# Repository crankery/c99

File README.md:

# Mini Mini Cortex 

***Note: Do not build this thing, I am just experimenting.***

Just a silly project really. Trying to squeeze Stuart Conner's [Mini Cortex](https://www.stuartconner.me.uk/mini_cortex/mini_cortex.htm) down
to a smaller form factor. Really, for no good reason.

I am going to attempt to add a different storage mechanism as CF cards are a bit hard to work with these days. To this end, there's an expansion
connector on this thing which is intended to have a stack of expansions plugged in from below.

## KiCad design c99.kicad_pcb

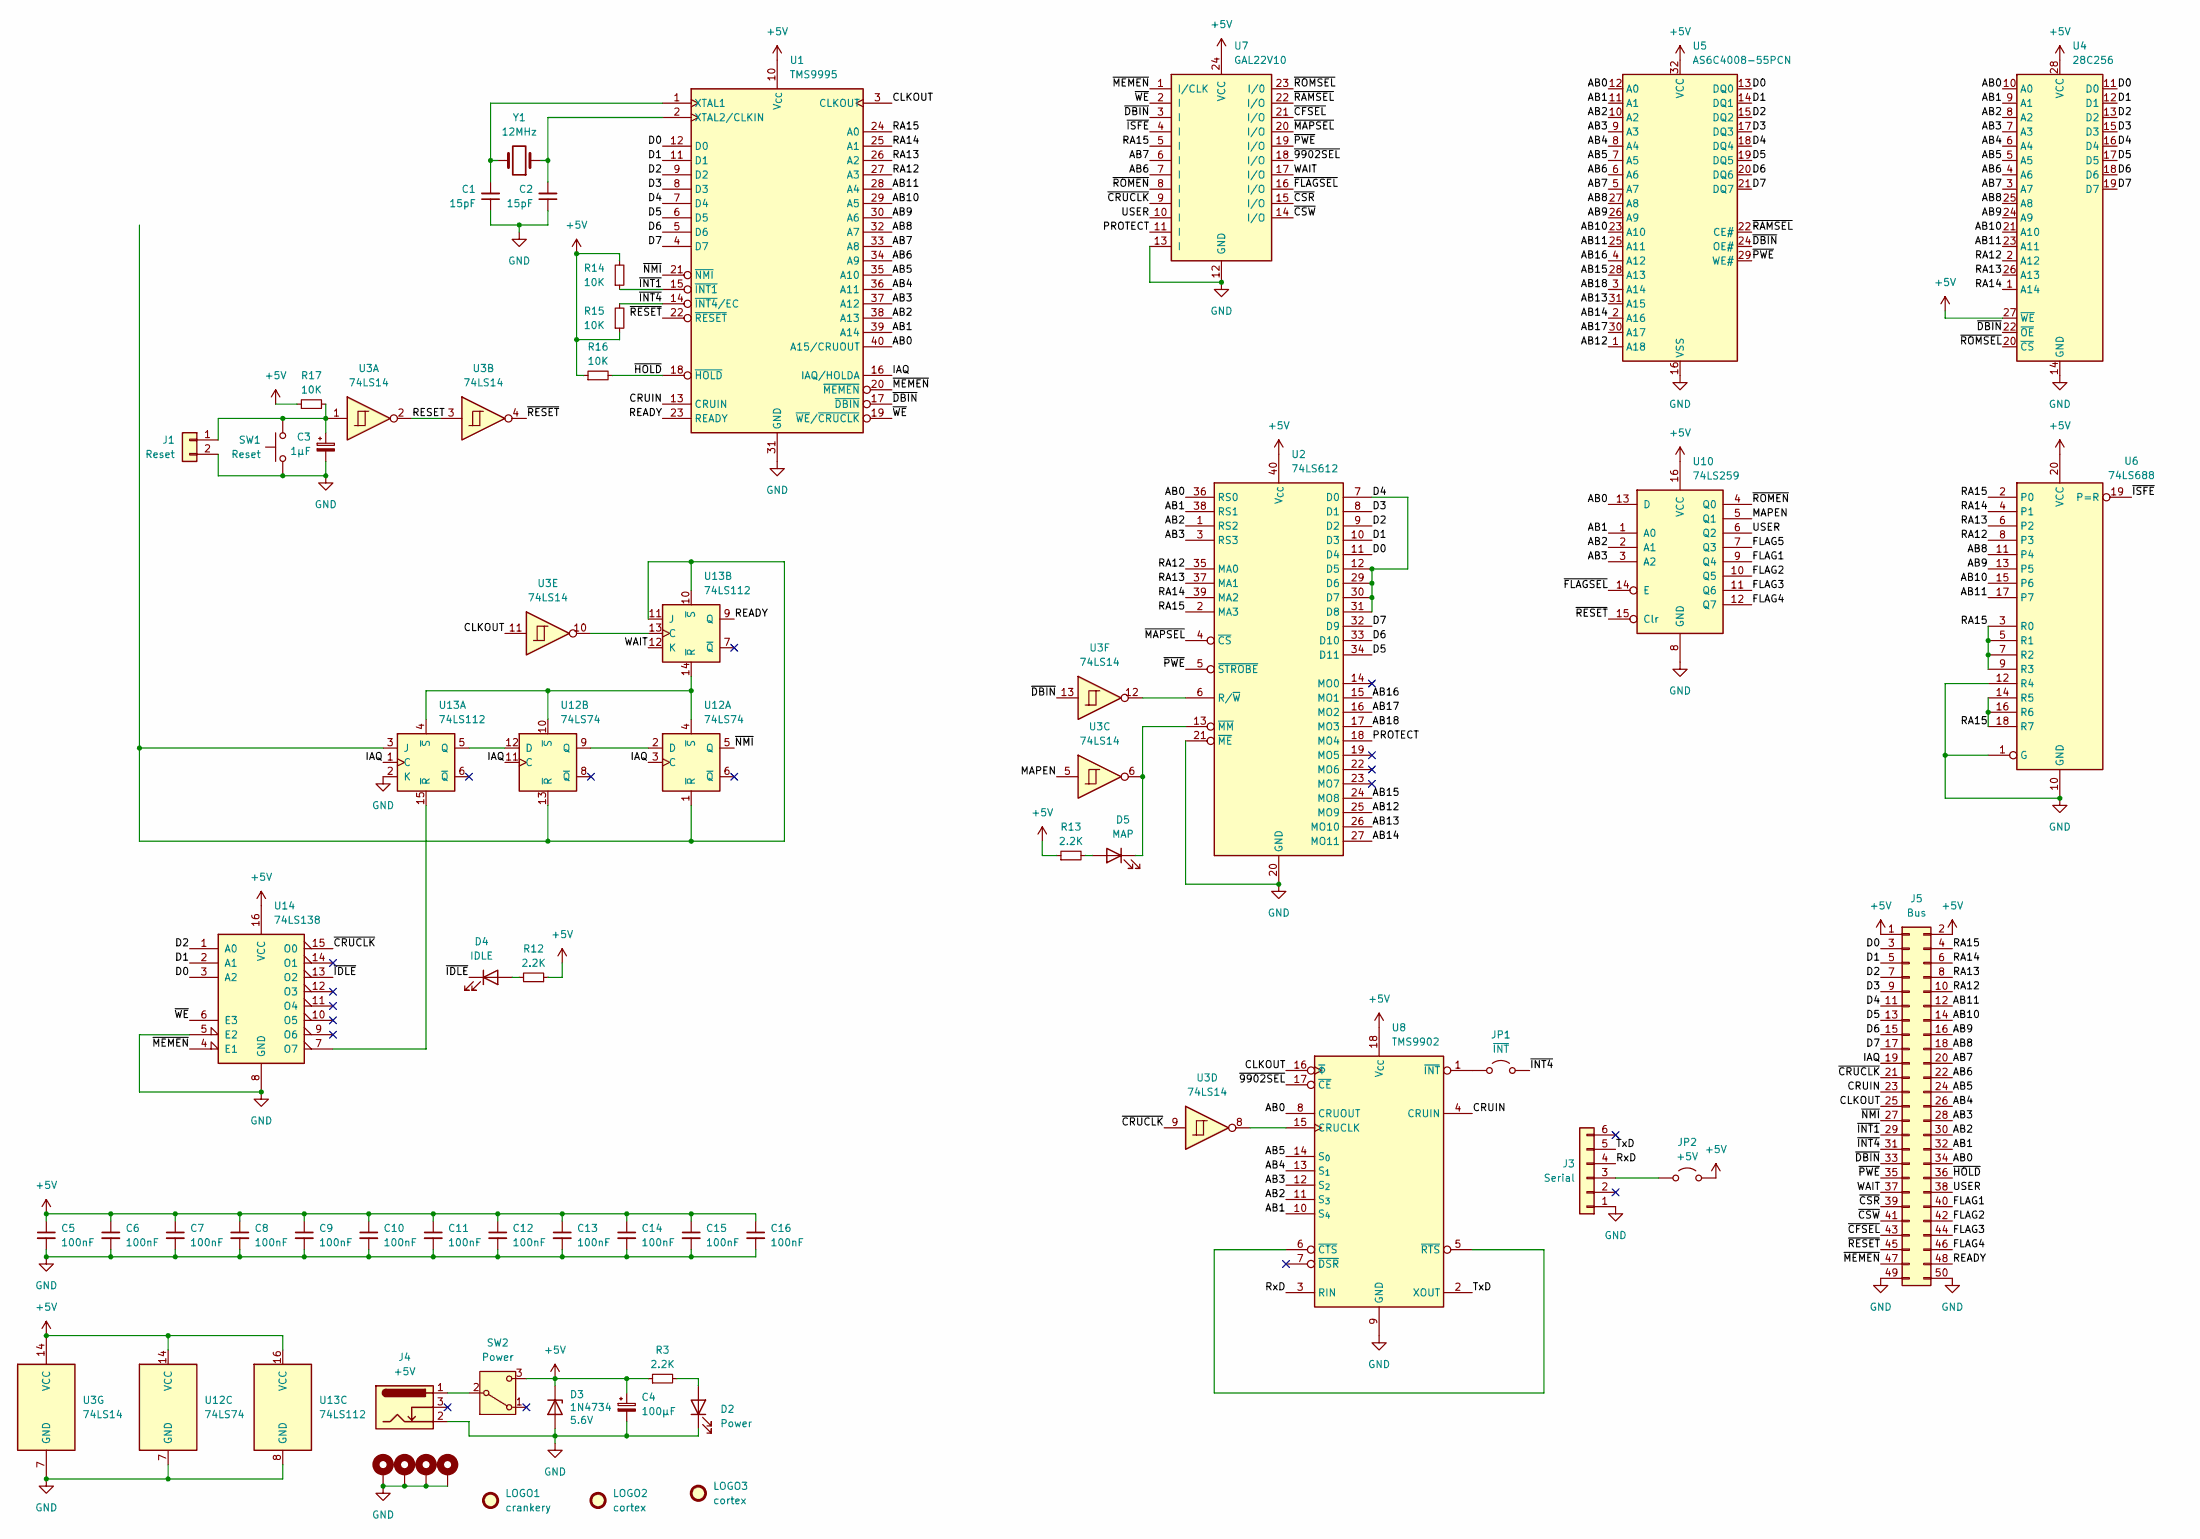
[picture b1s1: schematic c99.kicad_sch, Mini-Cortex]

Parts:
C1, C2: 15pF; C_Disc_D4.3mm_W1.9mm_P5.00mm
C3: 1µF; CP_Radial_D5.0mm_P2.00mm
C4: 100µF; CP_Radial_D5.0mm_P2.00mm
C5, C6, C7, C8, C9, C10, C11, C12, C13, C14, C15, C16: 100nF; C_Disc_D4.3mm_W1.9mm_P5.00mm
D2: Power; LED_D3.0mm
D3: 1N4734; D_DO-41_SOD81_P7.62mm_Horizontal
D4: IDLE; LED_D3.0mm
D5: MAP; LED_D3.0mm
H1, H2, H3, H4: MountingHole_Pad; MountingHole_2.7mm_M2.5_DIN965_Pad
J1: Reset; JST_PH_B2B-PH-K_1x02_P2.00mm_Vertical
J3: Serial; PinSocket_1x06_P2.54mm_Horizontal
J4: +5V; BarrelJack_Horizontal
J5: Bus; PinHeader_2x25_P2.54mm_Vertical
JP1: ~{INT}; PinHeader_1x02_P2.54mm_Vertical
JP2: +5V; PinHeader_1x02_P2.54mm_Vertical
LOGO1: crankery; crankery_small
LOGO2: cortex
LOGO3: cortex; eti
R3, R12, R13: 2.2K; R_Axial_DIN0204_L3.6mm_D1.6mm_P5.08mm_Horizontal
R14, R15, R16, R17: 10K; R_Axial_DIN0204_L3.6mm_D1.6mm_P5.08mm_Horizontal
SW1: Reset; SW_Tactile_SPST_Angled_PTS645Vx39-2LFS
SW2: Power; SW_2AS1T2A1M6QES
U1: TMS9995; DIP-40_W15.24mm
U2: 74LS612; DIP-40_W15.24mm
U3: 74LS14; DIP-14_W7.62mm
U4: 28C256; DIP-28_W15.24mm
U5: AS6C4008-55PCN; DIP-32_W15.24mm
U6: 74LS688; DIP-20_W7.62mm
U7: GAL22V10; DIP-24_W7.62mm
U8: TMS9902; DIP-18_W7.62mm
U10: 74LS259; DIP-16_W7.62mm
U12: 74LS74; DIP-14_W7.62mm
U13: 74LS112; DIP-16_W7.62mm
U14: 74LS138; DIP-16_W7.62mm
Y1: 12MHz; Crystal_HC49-U_Vertical

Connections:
+5V: C4.1, C5.1, C6.1, C7.1, C8.1, C9.1, C10.1, C11.1, C12.1, C13.1, C14.1, C15.1, C16.1, D3.1 (K), J5.1, J5.2, JP2.2 (B), R3.1, R12.1, R13.1, R14.2, R15.1, R16.1, R17.1, SW2.3 (C), U1.10 (V_{CC}), U2.40 (V_{CC}), U3.14 (VCC), U4.27 (~WE), U4.28 (VCC), U5.32 (VCC), U6.20 (VCC), U7.24 (VCC), U8.18 (V_{CC}), U10.16 (VCC), U12.14 (VCC), U13.16 (VCC), U14.16 (VCC)
/AB0: J5.34, U1.40 (A15/CRUOUT), U2.36 (RS0), U4.10 (A0), U5.12 (A0), U8.8 (CRUOUT), U10.13 (D)
/AB1: J5.32, U1.39 (A14), U2.38 (RS1), U4.9 (A1), U5.11 (A1), U8.10 (S_{4}), U10.1 (A0)
/AB2: J5.30, U1.38 (A13), U2.1 (RS2), U4.8 (A2), U5.10 (A2), U8.11 (S_{3}), U10.2 (A1)
/AB3: J5.28, U1.37 (A12), U2.3 (RS3), U4.7 (A3), U5.9 (A3), U8.12 (S_{2}), U10.3 (A2)
/AB4: J5.26, U1.36 (A11), U4.6 (A4), U5.8 (A4), U8.13 (S_{1})
/AB5: J5.24, U1.35 (A10), U4.5 (A5), U5.7 (A5), U8.14 (S_{0})
/AB6: J5.22, U1.34 (A9), U4.4 (A6), U5.6 (A6), U7.7 (I)
/AB7: J5.20, U1.33 (A8), U4.3 (A7), U5.5 (A7), U7.6 (I)
/AB8: J5.18, U1.32 (A7), U4.25 (A8), U5.27 (A8), U6.11 (P4)
/AB9: J5.16, U1.30 (A6), U4.24 (A9), U5.26 (A9), U6.13 (P5)
/AB10: J5.14, U1.29 (A5), U4.21 (A10), U5.23 (A10), U6.15 (P6)
/AB11: J5.12, U1.28 (A4), U4.23 (A11), U5.25 (A11), U6.17 (P7)
/AB12: U2.25 (MO9), U5.1 (A18)
/AB13: U2.26 (MO10), U5.31 (A15)
/AB14: U2.27 (MO11), U5.2 (A16)
/AB15: U2.24 (MO8), U5.28 (A13)
/AB16: U2.15 (MO1), U5.4 (A12)
/AB17: U2.16 (MO2), U5.30 (A17)
/AB18: U2.17 (MO3), U5.3 (A14)
/CLKOUT: J5.25, U1.3 (CLKOUT), U3.11, U8.16 (~Φ)
/CRUIN: J5.23, U1.13 (CRUIN), U8.4 (CRUIN)
/D0: J5.3, U1.12 (D0), U2.11 (D4), U4.11 (D0), U5.13 (DQ0), U14.3 (A2)
/D1: J5.5, U1.11 (D1), U2.10 (D3), U4.12 (D1), U5.14 (DQ1), U14.2 (A1)
/D2: J5.7, U1.9 (D2), U2.9 (D2), U4.13 (D2), U5.15 (DQ2), U14.1 (A0)
/D3: J5.9, U1.8 (D3), U2.8 (D1), U4.15 (D3), U5.17 (DQ3)
/D4: J5.11, U1.7 (D4), U2.7 (D0), U2.12 (D5), U2.29 (D6), U2.30 (D7), U2.31 (D8), U4.16 (D4), U5.18 (DQ4)
/D5: J5.13, U1.6 (D5), U2.34 (D11), U4.17 (D5), U5.19 (DQ5)
/D6: J5.15, U1.5 (D6), U2.33 (D10), U4.18 (D6), U5.20 (DQ6)
/D7: J5.17, U1.4 (D7), U2.32 (D9), U4.19 (D7), U5.21 (DQ7)
/FLAG1: J5.40, U10.9 (Q4)
/FLAG2: J5.42, U10.10 (Q5)
/FLAG3: J5.44, U10.11 (Q6)
/FLAG4: J5.46, U10.12 (Q7)
/FLAG5: U10.7 (Q3)
/IAQ: J5.19, U1.16 (IAQ/HOLDA), U12.3 (C), U12.11 (C), U13.1 (C)
/MAPEN: U3.5, U10.5 (Q1)
/PROTECT: U2.18 (MO4), U7.11 (I)
/RA12: J5.10, U1.27 (A3), U2.35 (MA0), U4.2 (A12), U6.8 (P3)
/RA13: J5.8, U1.26 (A2), U2.37 (MA1), U4.26 (A13), U6.6 (P2)
/RA14: J5.6, U1.25 (A1), U2.39 (MA2), U4.1 (A14), U6.4 (P1)
/RA15: J5.4, U1.24 (A0), U2.2 (MA3), U6.2 (P0), U6.3 (R0), U6.5 (R1), U6.7 (R2), U6.9 (R3), U6.14 (R5), U6.16 (R6), U6.18 (R7), U7.5 (I)
/READY: J5.48, U1.23 (READY), U13.9 (Q)
/RESET: U3.2, U3.3
/RxD: J3.4, U8.3 (RIN)
/TxD: J3.5, U8.2 (XOUT)
/USER: J5.38, U7.10 (I), U10.6 (Q2)
/WAIT: J5.37, U7.17 (I/O), U13.12 (K)
/~9902SEL: U7.18 (I/O), U8.17 (~CE)
/~CFSEL: J5.43, U7.21 (I/O)
/~CRUCLK: J5.21, U3.9, U7.9 (I), U14.15 (O0)
/~CSR: J5.39, U7.15 (I/O)
/~CSW: J5.41, U7.14 (I/O)
/~DBIN: J5.33, U1.17 (~DBIN), U3.13, U4.22 (~OE), U5.24 (OE#), U7.3 (I)
/~FLAGSEL: U7.16 (I/O), U10.14 (E)
/~HOLD: J5.36, R16.2, U1.18 (~HOLD)
/~IDLE: D4.1 (K), U14.13 (O2)
/~INT1: J5.29, R14.1, U1.15 (~INT1)
/~INT4: J5.31, JP1.2 (B), R15.2, U1.14 (~INT4/EC)
/~ISFE: U6.19 (P=R), U7.4 (I)
/~MAPSEL: U2.4 (~CS), U7.20 (I/O)
/~MEMEN: J5.47, U1.20 (~MEMEN), U7.1 (I/CLK), U14.4 (E1)
/~NMI: J5.27, U1.21 (~NMI), U12.5 (Q)
/~PWE: J5.35, U2.5 (~STROBE), U5.29 (WE#), U7.19 (I/O)
/~RAMSEL: U5.22 (CE#), U7.22 (I/O)
/~RESET: J5.45, U1.22 (~RESET), U3.4, U10.15 (Clr)
/~ROMEN: U7.8 (I), U10.4 (Q0)
/~ROMSEL: U4.20 (~CS), U7.23 (I/0)
/~WE: U1.19 (~WE/~CRUCLK), U7.2 (I), U14.6 (E3)
GND: C1.1, C2.1, C3.2, C4.2, C5.2, C6.2, C7.2, C8.2, C9.2, C10.2, C11.2, C12.2, C13.2, C14.2, C15.2, C16.2, D2.1 (K), D3.2 (A), H1.1 (1_1), H2.1 (1_1), H3.1 (1_1), H4.1 (1_1), J1.2, J3.1, J4.2, J5.49, J5.50, SW1.1, U1.31 (GND), U2.20 (GND), U2.21 (~ME), U3.7 (GND), U4.14 (GND), U5.16 (VSS), U6.1 (G), U6.10 (GND), U6.12 (R4), U7.12 (GND), U7.13 (I), U8.9 (GND), U10.8 (GND), U12.7 (GND), U13.2 (K), U13.8 (GND), U14.5 (E2), U14.8 (GND)
unnamed: D2.2 (A), R3.2
unnamed: D4.2 (A), R12.2
unnamed: D5.2 (A), R13.2
unnamed: D5.1 (K), U2.13 (~MM), U3.6
unnamed: C3.1, J1.1, R17.2, SW1.2, U3.1
unnamed: J3.3, JP2.1 (A)
unnamed: JP1.1 (A), U8.1 (~INT)
unnamed: J4.1, SW2.2 (B)
unnamed: C1.2, U1.1 (XTAL1), Y1.2
unnamed: C2.2, U1.2 (XTAL2/CLKIN), Y1.1
unnamed: U2.6 (R/~W), U3.12
unnamed: U3.8, U8.15 (CRUCLK)
unnamed: U8.5 (~RTS), U8.6 (~CTS)
unnamed: U12.2 (D), U12.9 (Q)
unnamed: U12.1 (~R), U12.13 (~R), U13.3 (J), U13.10 (~S), U13.11 (J)
unnamed: U12.4 (~S), U12.10 (~S), U13.4 (~S), U13.14 (~R)
unnamed: U12.12 (D), U13.5 (Q)
unnamed: U13.15 (~R), U14.7 (O7)
unnamed: U3.10, U13.13 (C)

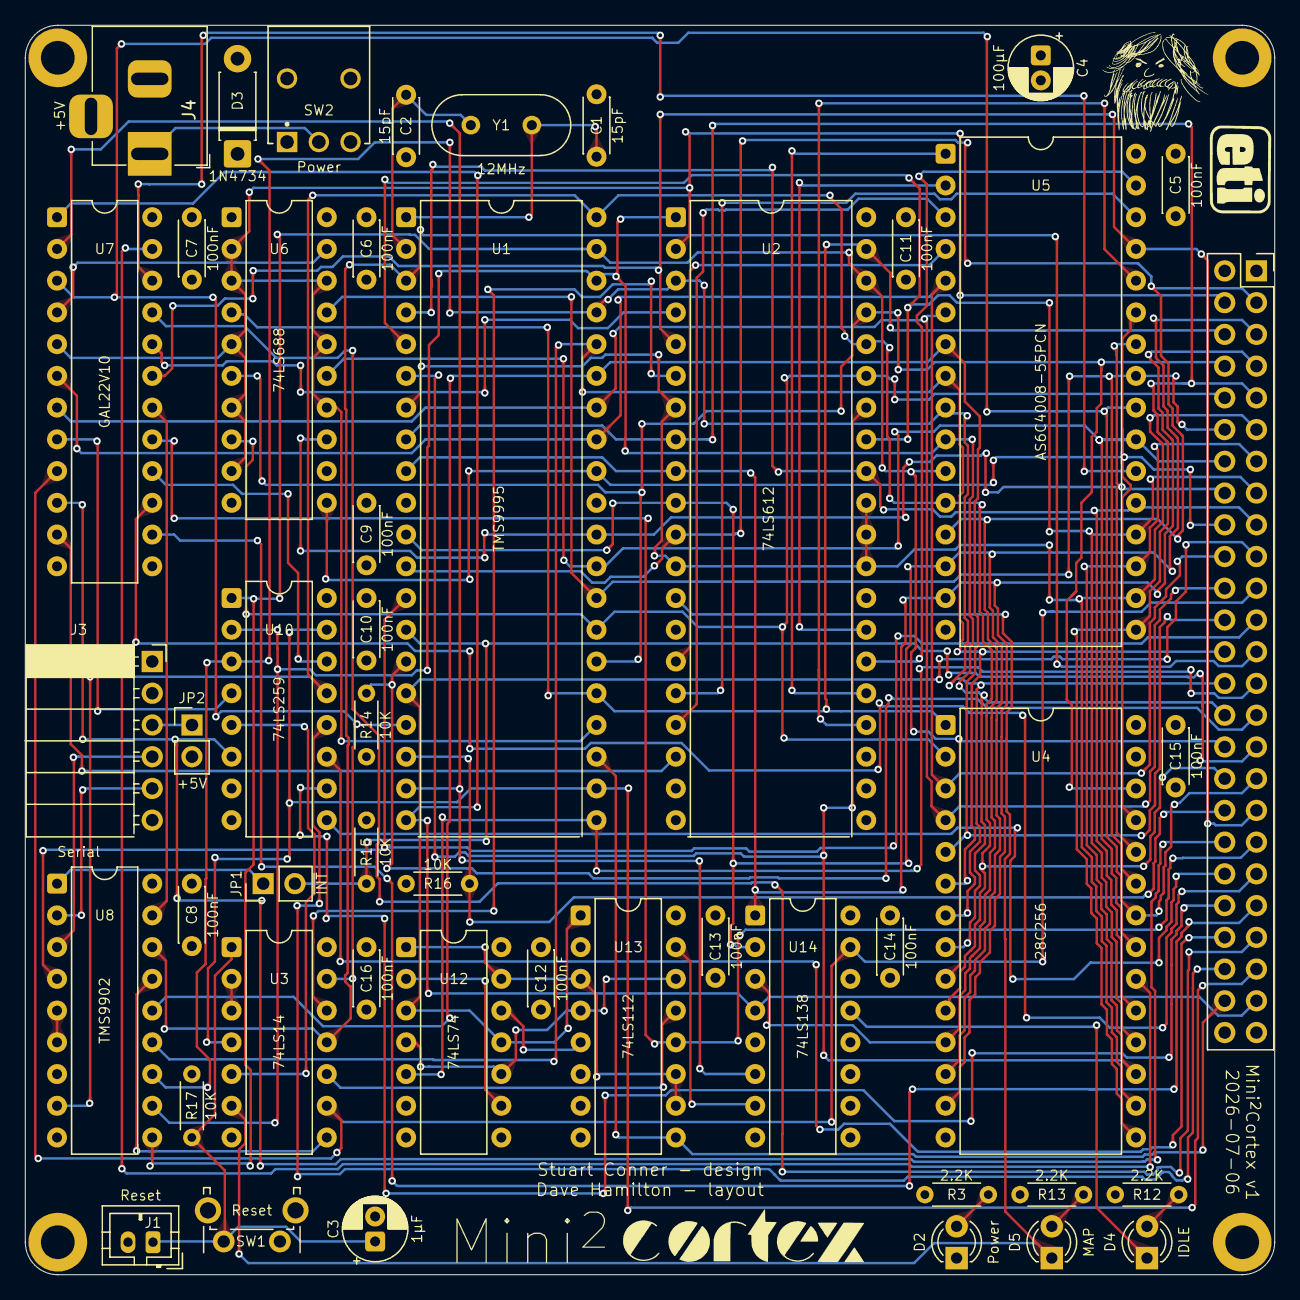
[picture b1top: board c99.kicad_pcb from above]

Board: 4 copper layers, 100.0 x 100.0 mm, 55 parts (1 on the bottom side), 88 nets.
